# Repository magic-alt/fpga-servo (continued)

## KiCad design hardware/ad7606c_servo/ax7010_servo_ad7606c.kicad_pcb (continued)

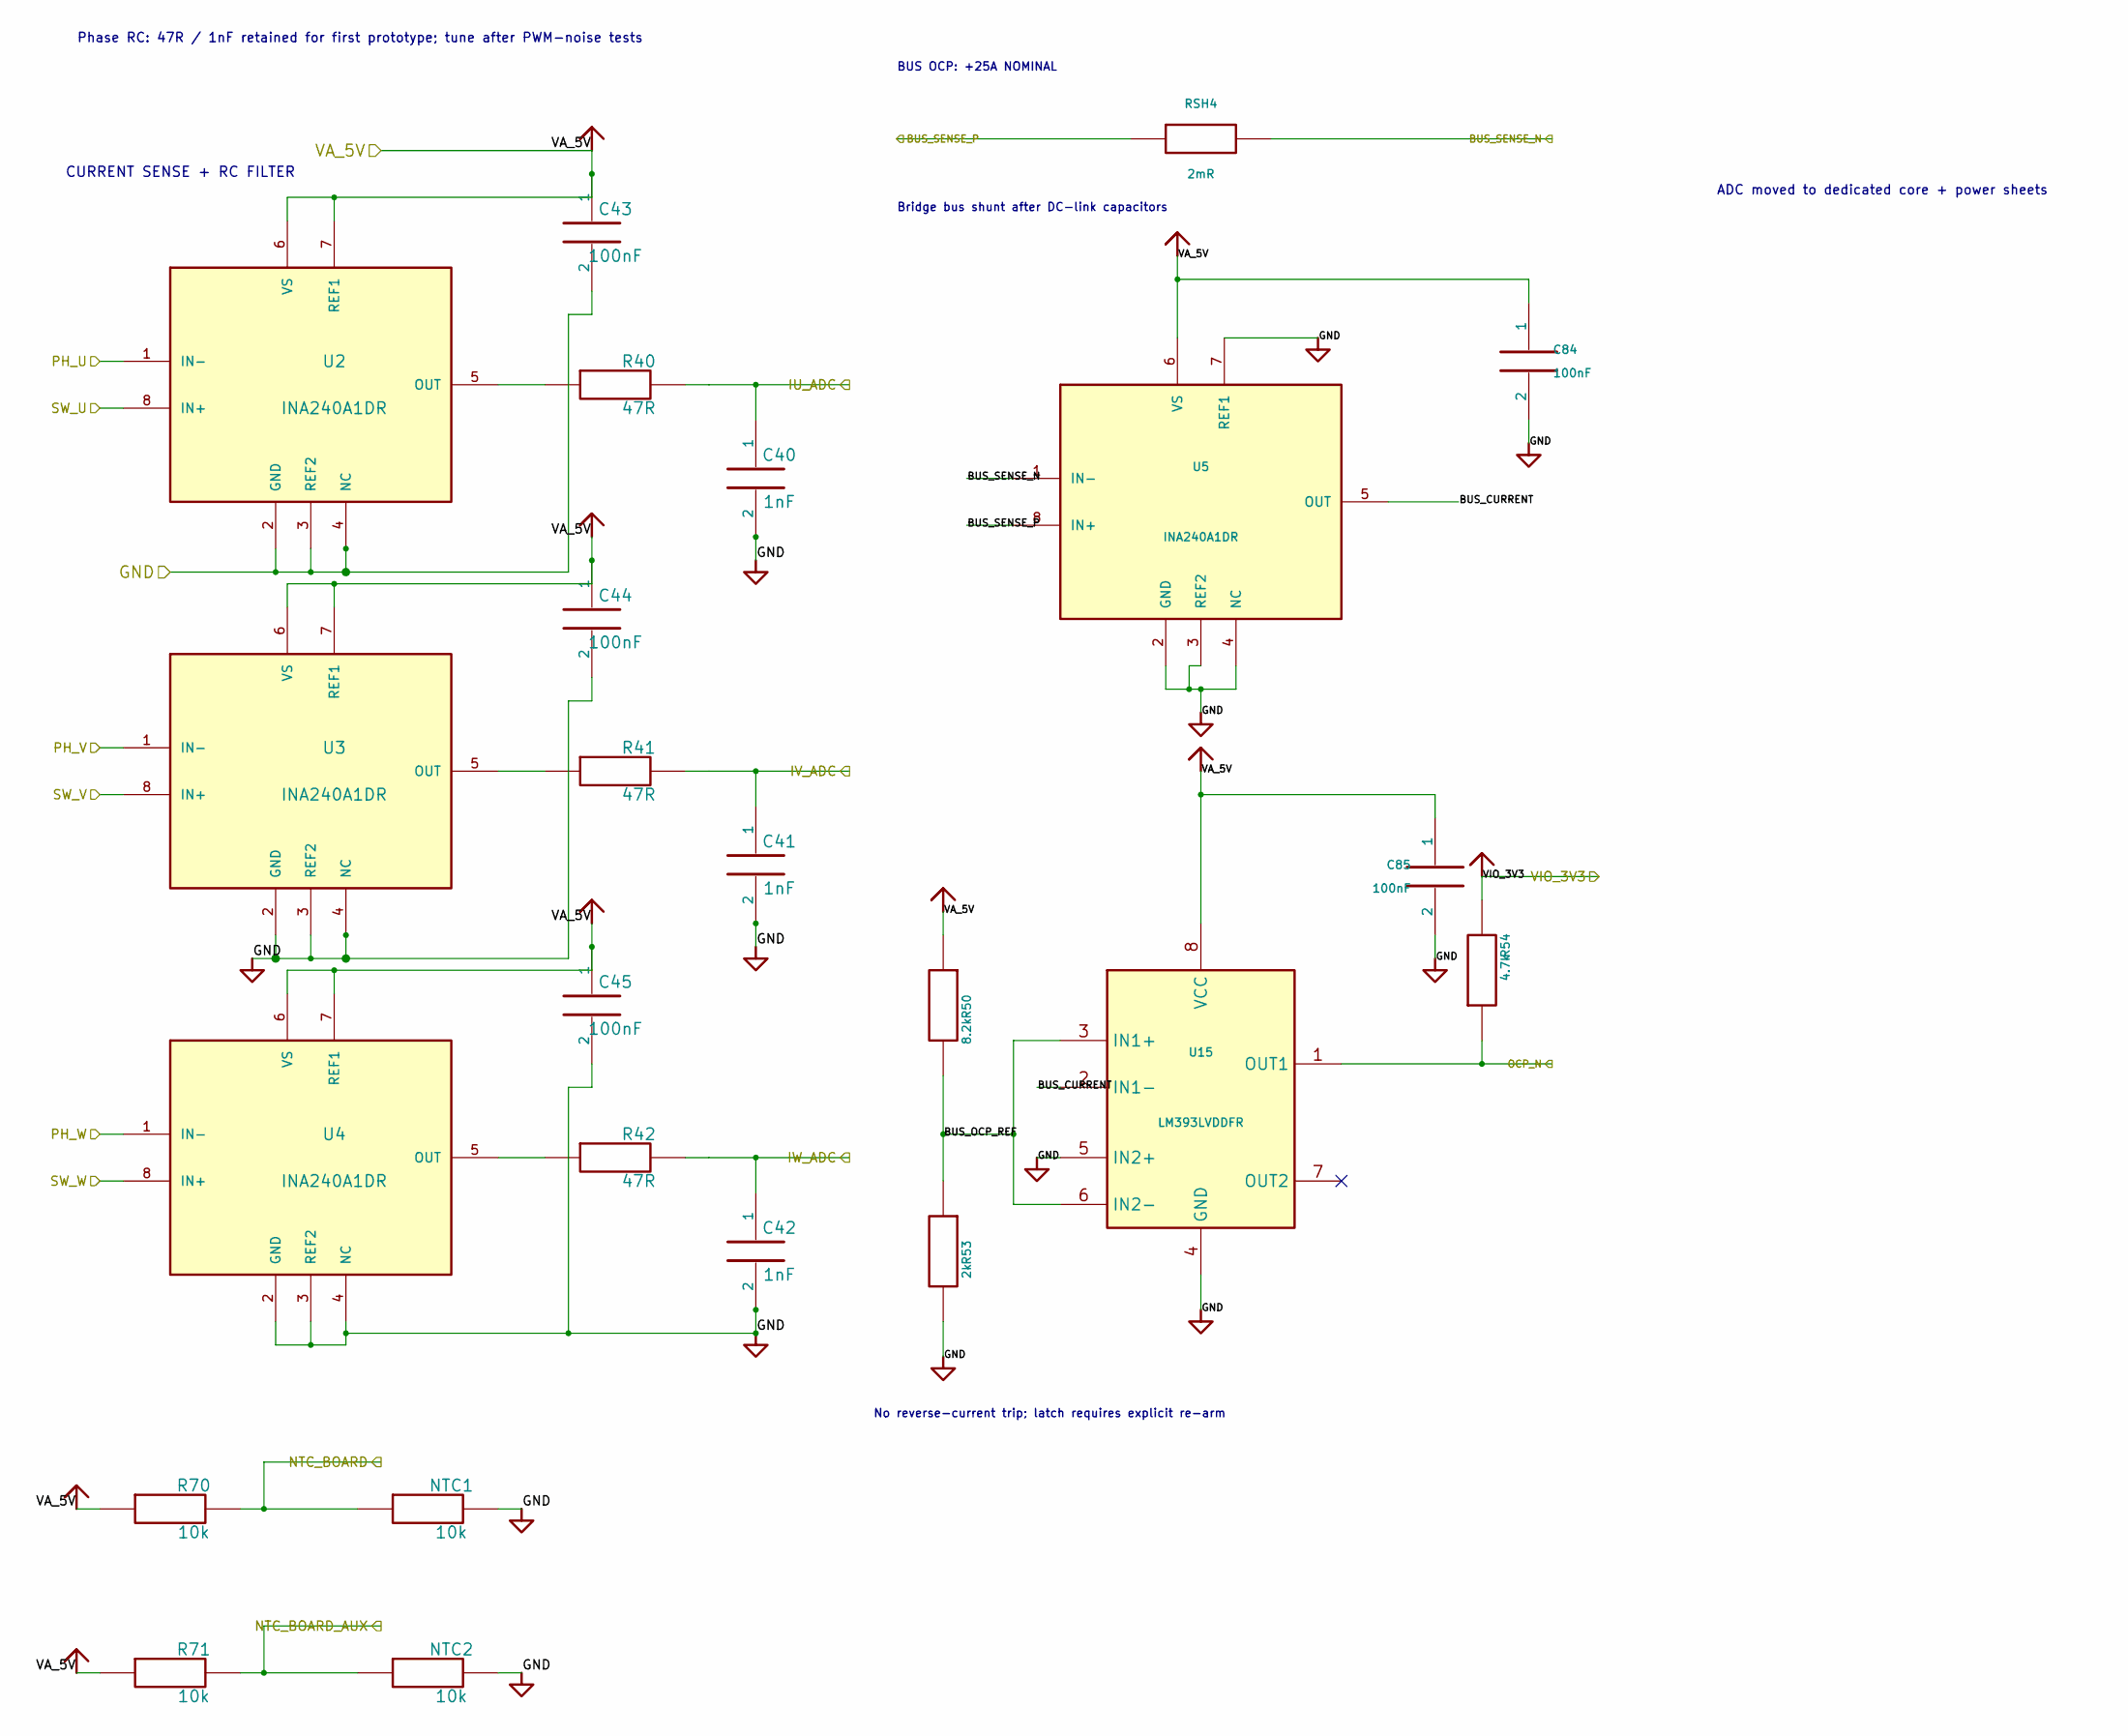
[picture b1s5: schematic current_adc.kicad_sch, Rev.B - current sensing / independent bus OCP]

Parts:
C40, C41, C42: 1nF; C_0603_1608Metric; MPN 0603CG102J101NT; LCSC C88489
C43, C44, C45, C84, C85: 100nF; C_0603_1608Metric; MPN 0603B104K500NT; LCSC C30926
NTC1, NTC2: 10k; NTC_0603_Shiheng_KUU; MPN CMFA 103F3950; LCSC C2889049
R40, R41, R42: 47R; R_0603_1608Metric; MPN RS-03K47R0FT; LCSC C140087
R50: 8.2k; R_0603_1608Metric; Tolerance 0.1%; MPN PTFR0603B8K20P9; LCSC C351624
R53: 2k; R_0603_1608Metric; Tolerance 0.1%; MPN TD03G2001BT; LCSC C666953
R54: 4.7k; R_0603_1608Metric; MPN RS-03K4701FT; LCSC C116693
R70, R71: 10k; R_0603_1608Metric; MPN TD03G1002BT; LCSC C667034
RSH4: 2mR; HoYLR2512_Kelvin; MPN HoYLR2512-3W-2mR-1%; LCSC C5375458
U2, U3, U4, U5: INA240A1DR; TI_D0008A_SOIC8_P1.27mm; MPN INA240A1DR; LCSC C2060769
U15: LM393LVDDFR; TI_DDF0008A; MPN LM393LVDDFR; LCSC C5213974

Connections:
/GND: C40.2, C41.2, C42.2, C43.2, C44.2, C45.2, C84.2, C85.2, NTC1.2, NTC2.2, R53.2, U2.2 (GND), U2.3 (REF2), U2.4 (NC), U3.2 (GND), U3.3 (REF2), U3.4 (NC), U4.2 (GND), U4.3 (REF2), U4.4 (NC), U5.2 (GND), U5.3 (REF2), U5.4 (NC), U5.7 (REF1), U15.4 (GND), U15.5 (IN2+); also elsewhere on the board
/IU_ADC: C40.1, R40.2; also elsewhere on the board
/IV_ADC: C41.1, R41.2; also elsewhere on the board
/IW_ADC: C42.1, R42.2; also elsewhere on the board
/NTC_BOARD: NTC1.1, R70.2; also elsewhere on the board
/NTC_BOARD_AUX: NTC2.1, R71.2; also elsewhere on the board
/OCP_N: R54.1, U15.1 (OUT1); also elsewhere on the board
/PH_U: U2.1 (IN-); also elsewhere on the board
/PH_V: U3.1 (IN-); also elsewhere on the board
/PH_W: U4.1 (IN-); also elsewhere on the board
/SW_U: U2.8 (IN+); also elsewhere on the board
/SW_V: U3.8 (IN+); also elsewhere on the board
/SW_W: U4.8 (IN+); also elsewhere on the board
/VA_5V: C43.1, C44.1, C45.1, C84.1, C85.1, R50.1, R70.1, R71.1, U2.6 (VS), U2.7 (REF1), U3.6 (VS), U3.7 (REF1), U4.6 (VS), U4.7 (REF1), U5.6 (VS), U15.8 (VCC); also elsewhere on the board
/VBUS_BRIDGE: RSH4.2, U5.1 (IN-); also elsewhere on the board
/VBUS_PROT: RSH4.1, U5.8 (IN+); also elsewhere on the board
/VIO_3V3: R54.2; also elsewhere on the board
/current_adc/BUS_CURRENT: U5.5 (OUT), U15.2 (IN1-)
/current_adc/BUS_OCP_REF: R50.2, R53.1, U15.3 (IN1+), U15.6 (IN2-)
unnamed: R40.1, U2.5 (OUT)
unnamed: R41.1, U3.5 (OUT)
unnamed: R42.1, U4.5 (OUT)

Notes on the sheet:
CURRENT SENSE + RC FILTER
BUS OCP: +25A NOMINAL
No reverse-current trip; latch requires explicit re-arm
Bridge bus shunt after DC-link capacitors
ADC moved to dedicated core + power sheets
Phase RC: 47R / 1nF retained for first prototype; tune after PWM-noise tests

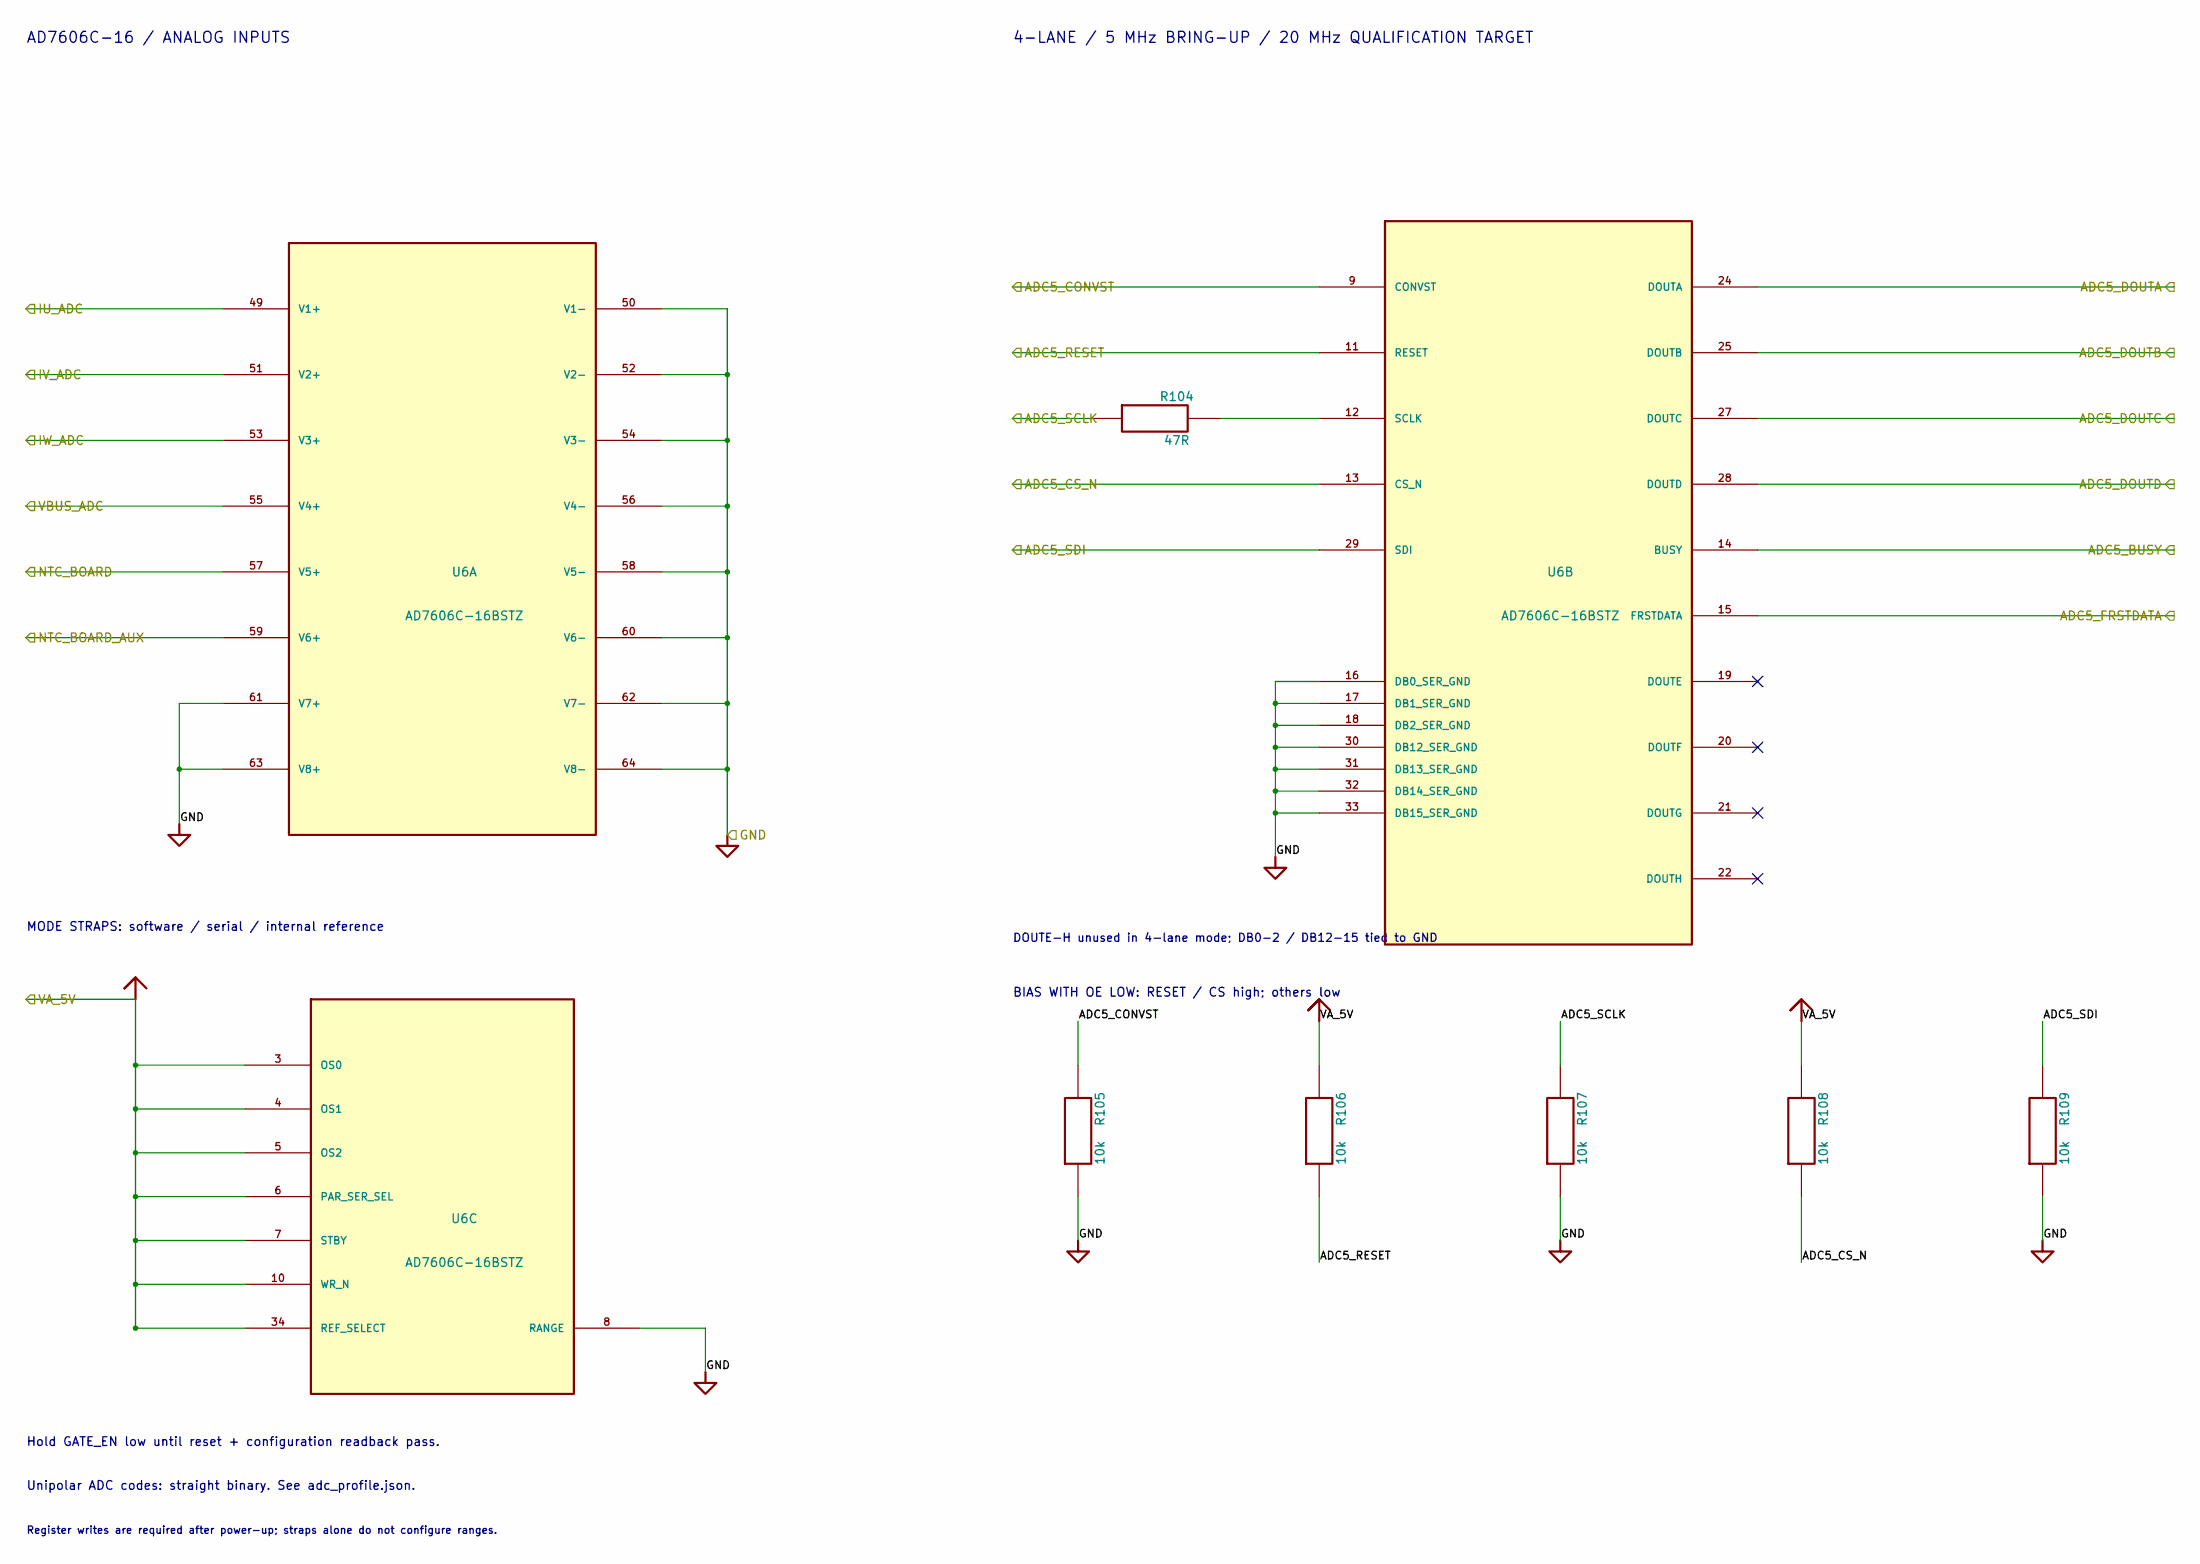
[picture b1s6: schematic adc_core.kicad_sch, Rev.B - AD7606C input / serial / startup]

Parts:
R104: 47R; R_0603_1608Metric; MPN RS-03K47R0FT; LCSC C140087
R105, R106, R107, R108, R109: 10k; R_0603_1608Metric; MPN ABD03K1002FT; LCSC C5139509
U6: AD7606C-16BSTZ; LQFP-64_10x10mm_P0.5mm; MPN AD7606C-16BSTZ; LCSC C5371769

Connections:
/ADC5_BUSY: U6.14 (BUSY); also elsewhere on the board
/ADC5_CONVST: R105.2, U6.9 (CONVST); also elsewhere on the board
/ADC5_CS_N: R108.1, U6.13 (CS_N); also elsewhere on the board
/ADC5_DOUTA: U6.24 (DOUTA); also elsewhere on the board
/ADC5_DOUTB: U6.25 (DOUTB); also elsewhere on the board
/ADC5_DOUTC: U6.27 (DOUTC); also elsewhere on the board
/ADC5_DOUTD: U6.28 (DOUTD); also elsewhere on the board
/ADC5_FRSTDATA: U6.15 (FRSTDATA); also elsewhere on the board
/ADC5_RESET: R106.1, U6.11 (RESET); also elsewhere on the board
/ADC5_SCLK: R104.1, R107.2; also elsewhere on the board
/ADC5_SDI: R109.2, U6.29 (SDI); also elsewhere on the board
/GND: R105.1, R107.1, R109.1, U6.8 (RANGE), U6.16 (DB0_SER_GND), U6.17 (DB1_SER_GND), U6.18 (DB2_SER_GND), U6.30 (DB12_SER_GND), U6.31 (DB13_SER_GND), U6.32 (DB14_SER_GND), U6.33 (DB15_SER_GND), U6.50 (V1-), U6.52 (V2-), U6.54 (V3-), U6.56 (V4-), U6.58 (V5-), U6.60 (V6-), U6.61 (V7+), U6.62 (V7-), U6.63 (V8+), U6.64 (V8-); also elsewhere on the board
/IU_ADC: U6.49 (V1+); also elsewhere on the board
/IV_ADC: U6.51 (V2+); also elsewhere on the board
/IW_ADC: U6.53 (V3+); also elsewhere on the board
/NTC_BOARD: U6.57 (V5+); also elsewhere on the board
/NTC_BOARD_AUX: U6.59 (V6+); also elsewhere on the board
/VA_5V: R106.2, R108.2, U6.3 (OS0), U6.4 (OS1), U6.5 (OS2), U6.6 (PAR_SER_SEL), U6.7 (STBY), U6.10 (WR_N), U6.34 (REF_SELECT); also elsewhere on the board
/VBUS_ADC: U6.55 (V4+); also elsewhere on the board
unnamed: R104.2, U6.12 (SCLK)

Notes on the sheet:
AD7606C-16 / ANALOG INPUTS
4-LANE / 5 MHz BRING-UP / 20 MHz QUALIFICATION TARGET
DOUTE-H unused in 4-lane mode; DB0-2 / DB12-15 tied to GND
MODE STRAPS: software / serial / internal reference
BIAS WITH OE LOW: RESET / CS high; others low
Hold GATE_EN low until reset + configuration readback pass.
Unipolar ADC codes: straight binary. See adc_profile.json.
Register writes are required after power-up; straps alone do not configure ranges.

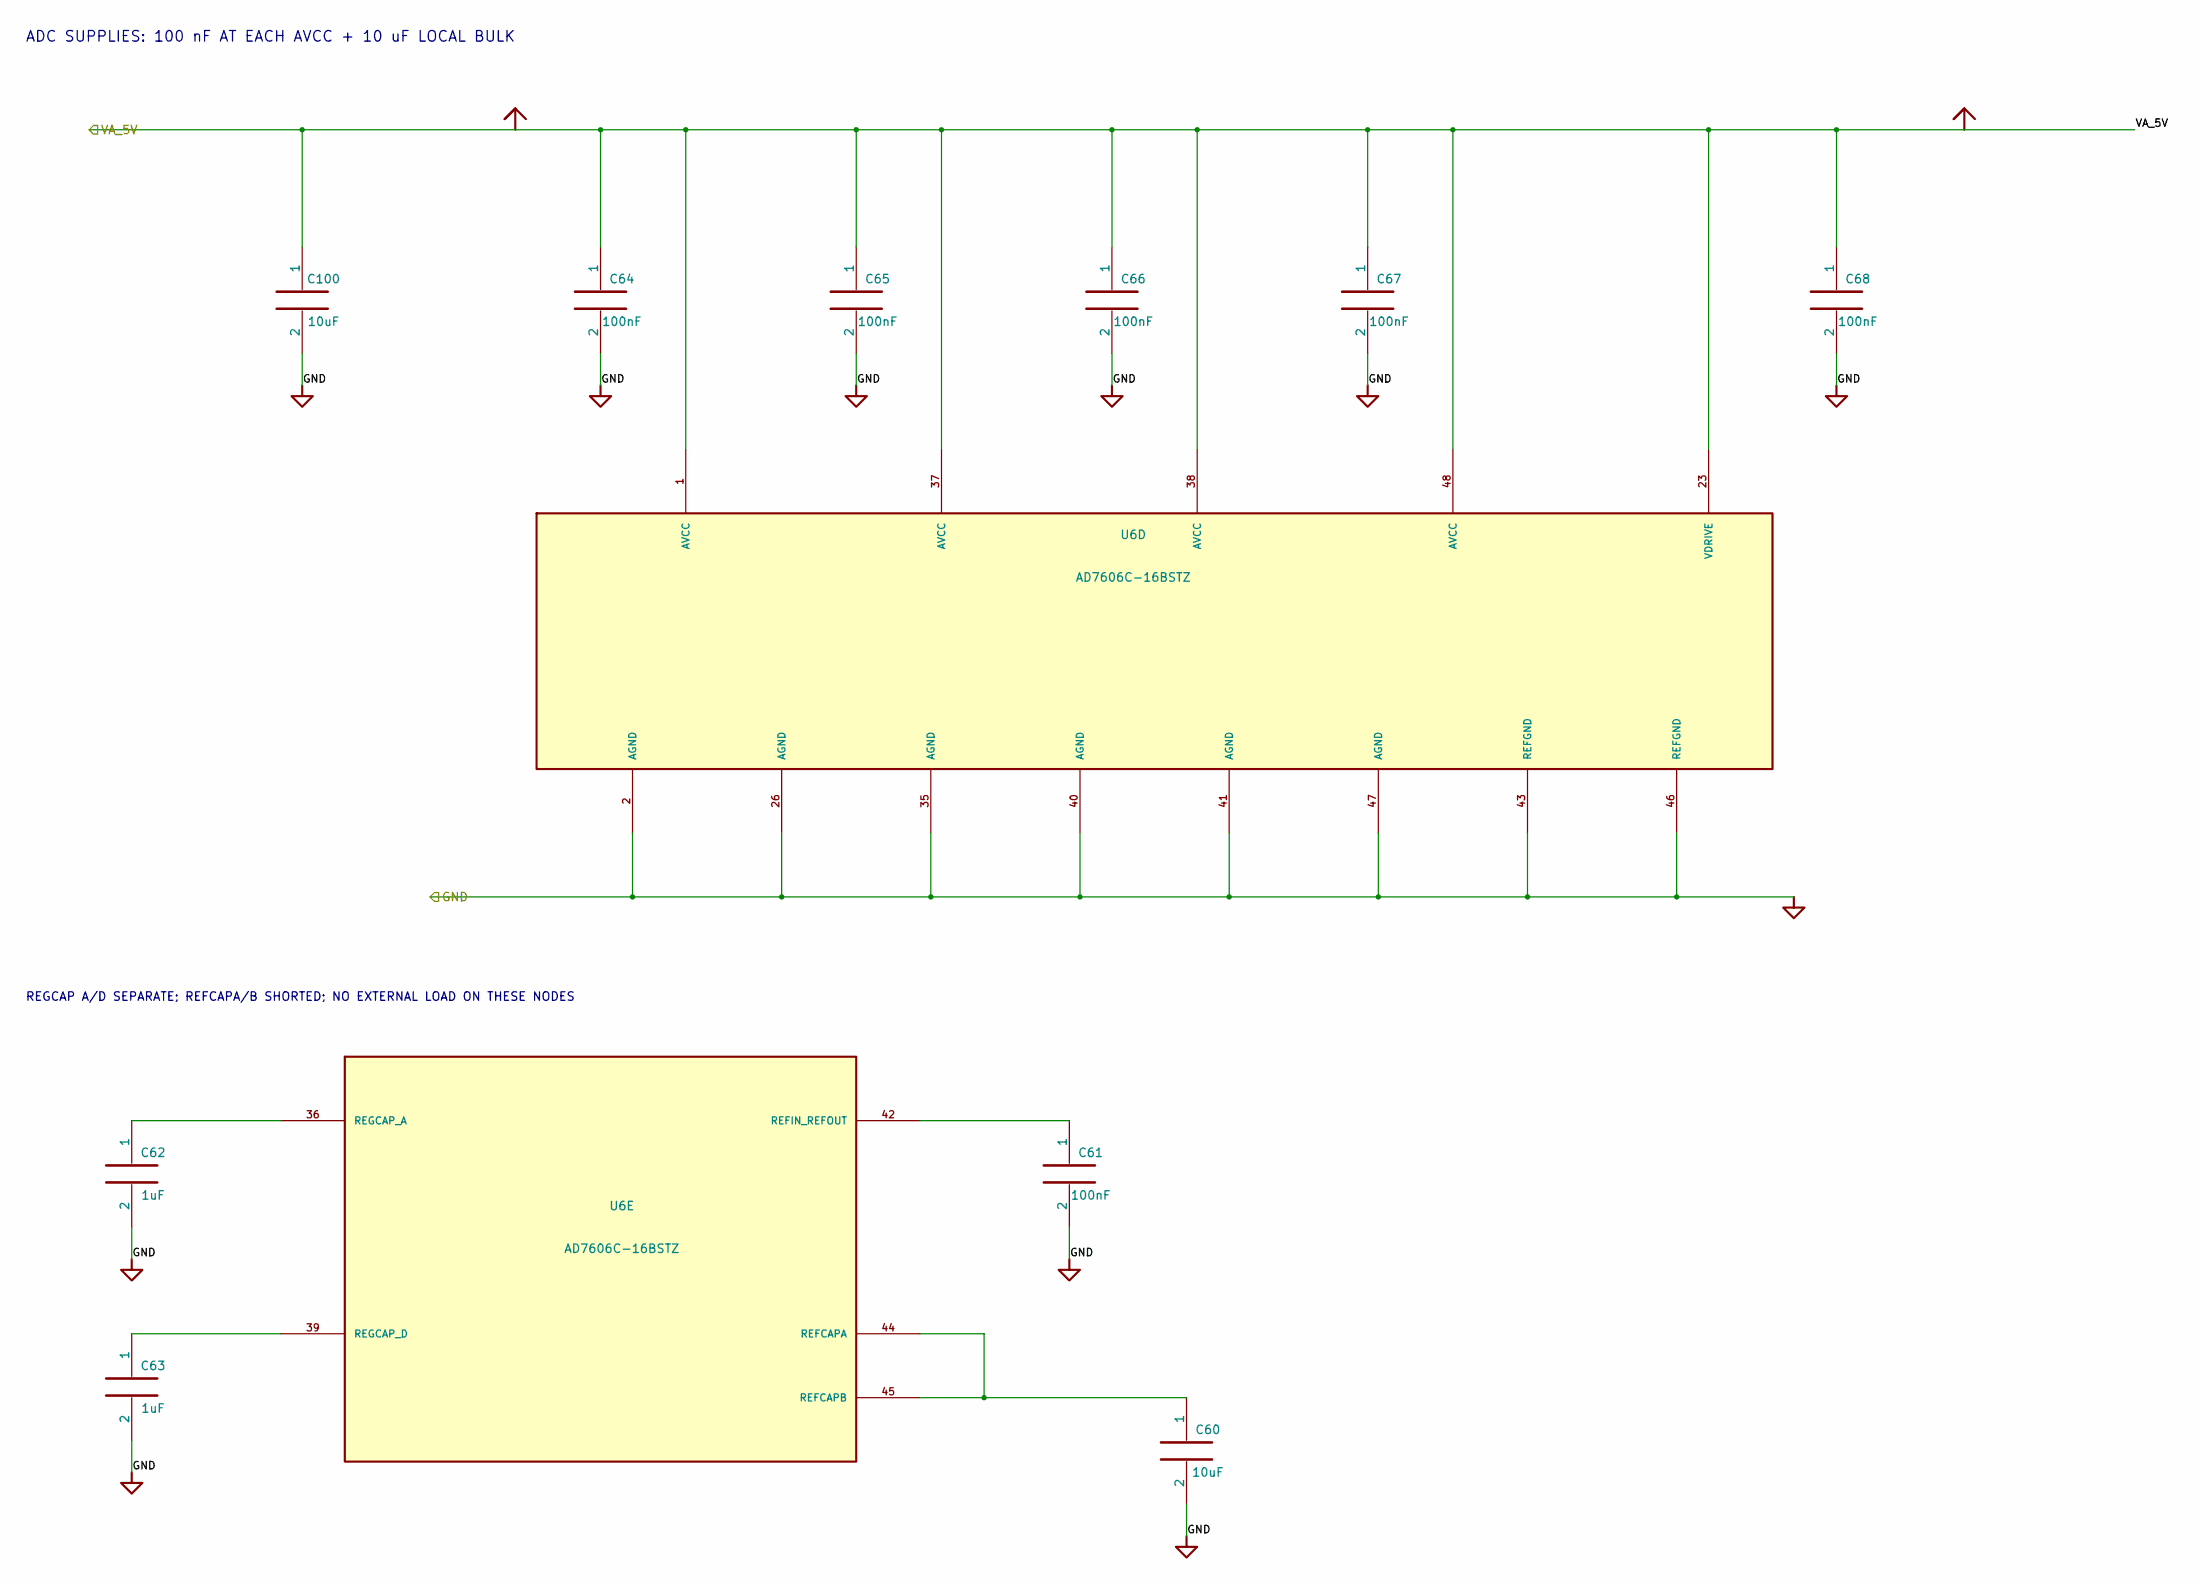
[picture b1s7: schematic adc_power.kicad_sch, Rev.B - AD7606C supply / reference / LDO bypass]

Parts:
C60, C100: 10uF; C_0805_2012Metric; MPN HGC0805R7106K250NSLJ; LCSC C33546010
C61, C64, C65, C66, C67, C68: 100nF; C_0603_1608Metric; MPN 0603B104K500NT; LCSC C30926
C62, C63: 1uF; C_0603_1608Metric; MPN 0603B105K250NT; LCSC C59302
U6: AD7606C-16BSTZ; LQFP-64_10x10mm_P0.5mm; MPN AD7606C-16BSTZ; LCSC C5371769

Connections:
/GND: C60.2, C61.2, C62.2, C63.2, C64.2, C65.2, C66.2, C67.2, C68.2, C100.2, U6.2 (AGND), U6.26 (AGND), U6.35 (AGND), U6.40 (AGND), U6.41 (AGND), U6.43 (REFGND), U6.46 (REFGND), U6.47 (AGND); also elsewhere on the board
/VA_5V: C64.1, C65.1, C66.1, C67.1, C68.1, C100.1, U6.1 (AVCC), U6.23 (VDRIVE), U6.37 (AVCC), U6.38 (AVCC), U6.48 (AVCC); also elsewhere on the board
unnamed: C60.1, U6.44 (REFCAPA), U6.45 (REFCAPB)
unnamed: C61.1, U6.42 (REFIN_REFOUT)
unnamed: C62.1, U6.36 (REGCAP_A)
unnamed: C63.1, U6.39 (REGCAP_D)

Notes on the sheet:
ADC SUPPLIES: 100 nF AT EACH AVCC + 10 uF LOCAL BULK
REGCAP A/D SEPARATE; REFCAPA/B SHORTED; NO EXTERNAL LOAD ON THESE NODES

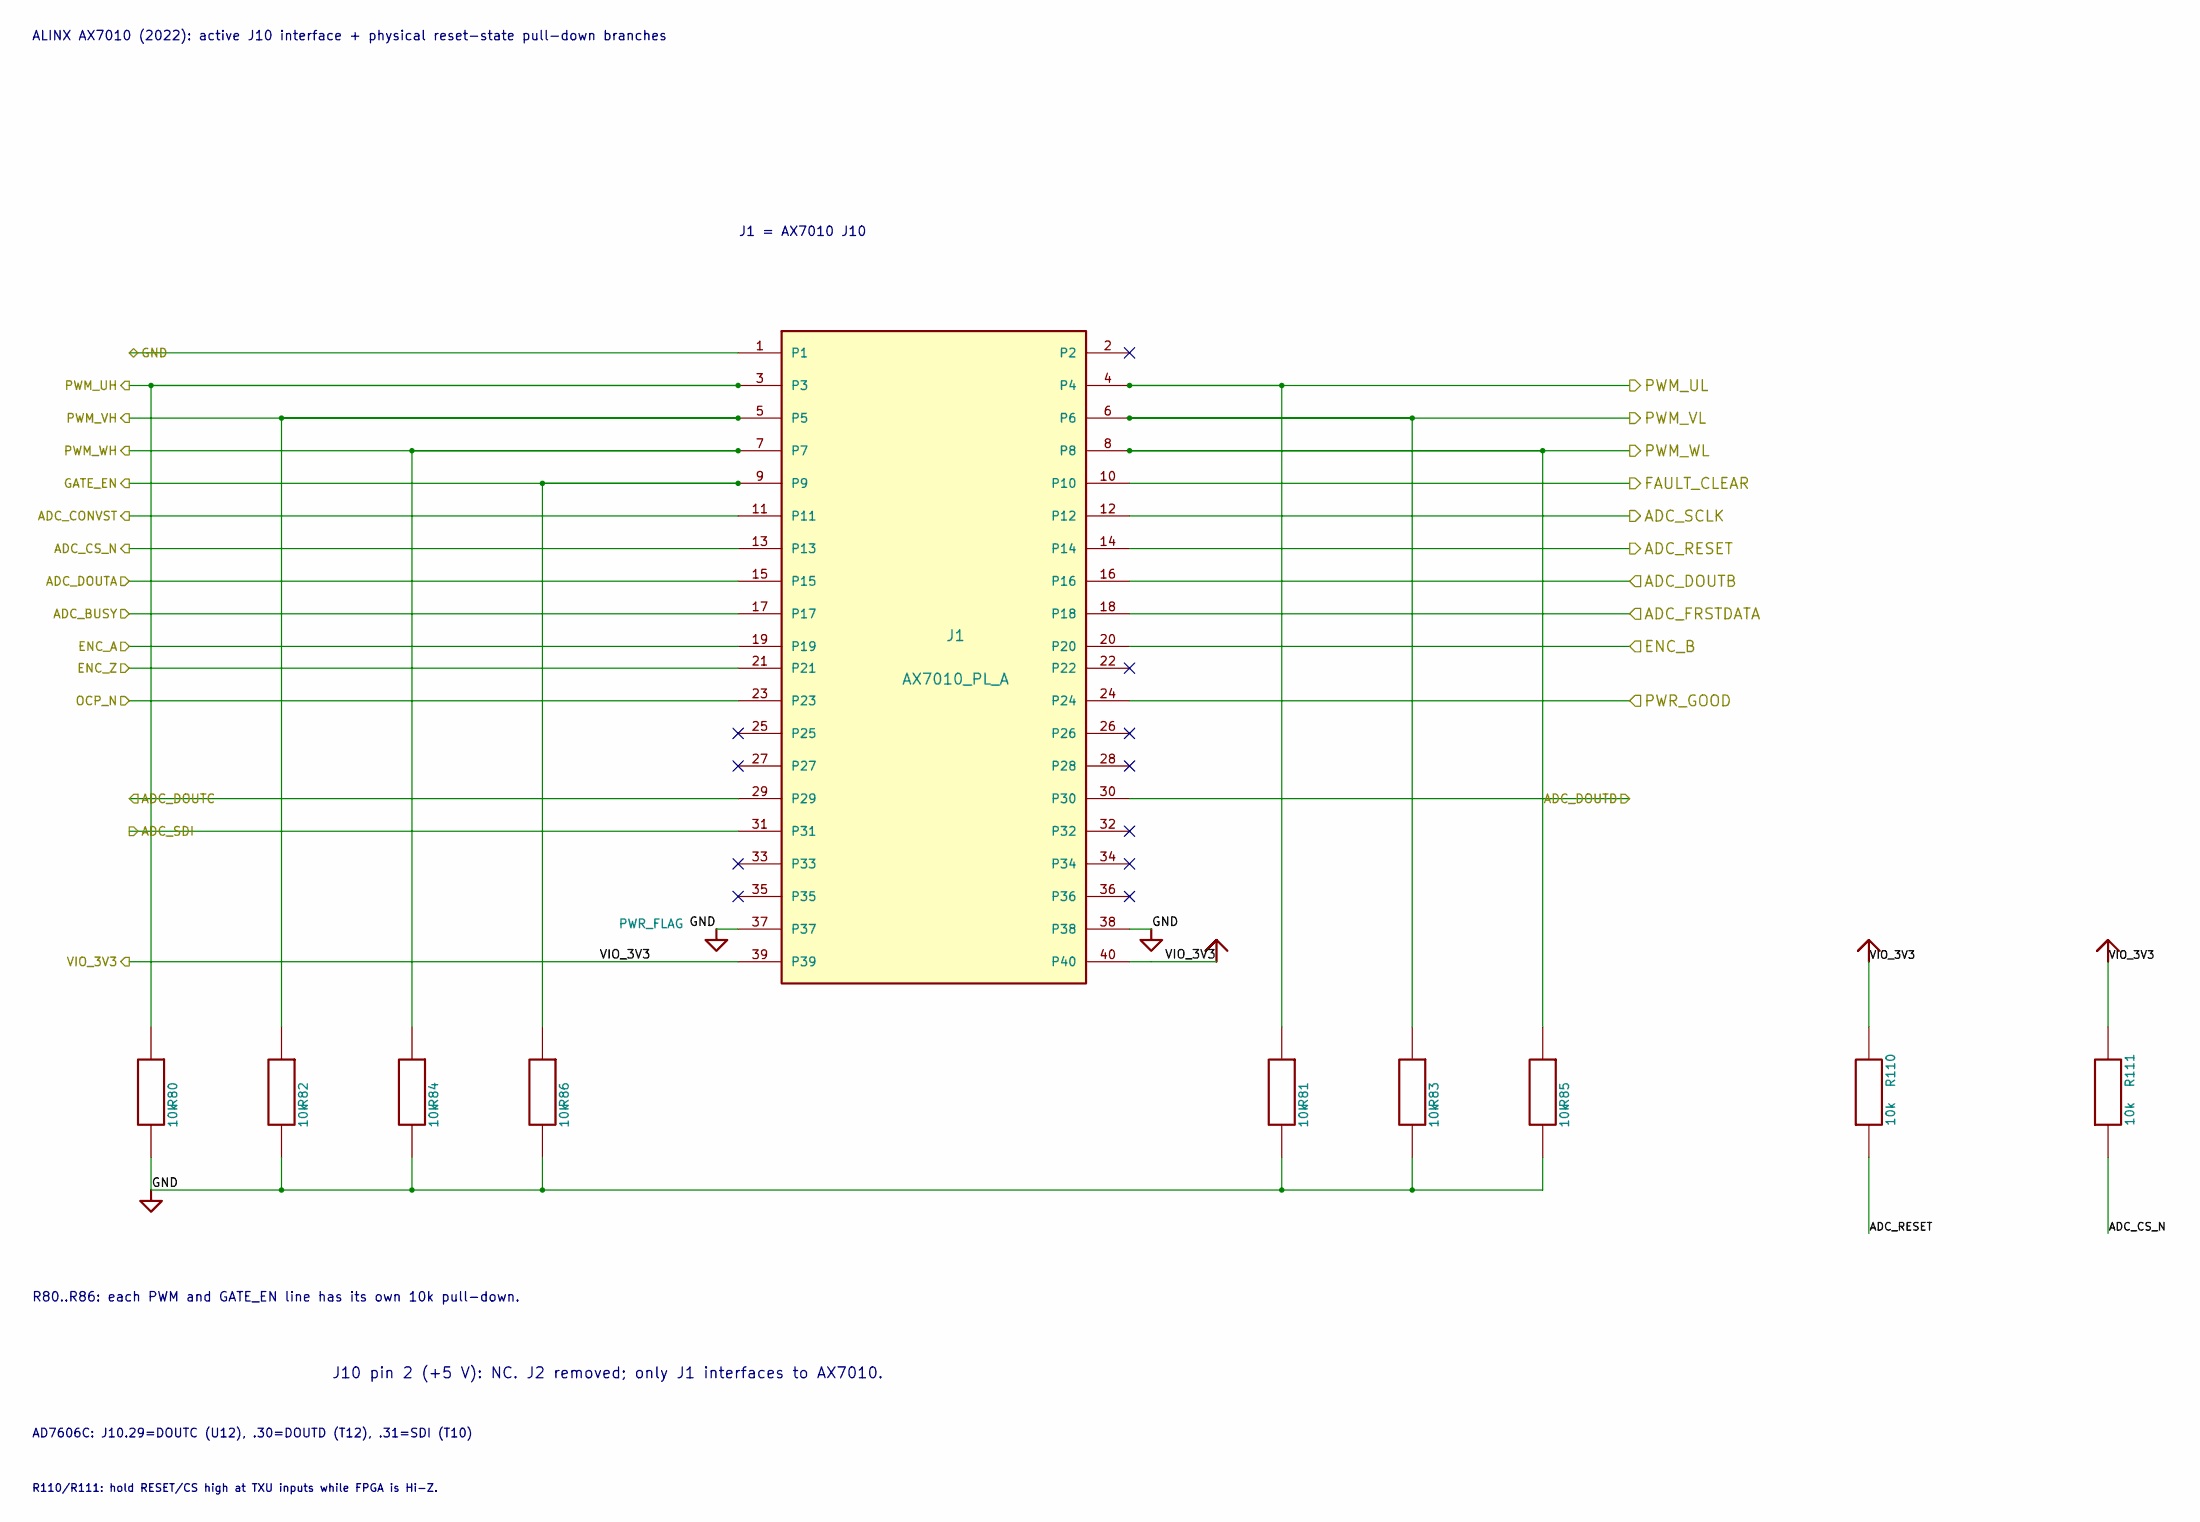
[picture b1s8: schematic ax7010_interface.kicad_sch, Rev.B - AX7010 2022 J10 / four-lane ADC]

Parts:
J1: AX7010_PL_A; JILN_3210_2x20_P2.54mm_D1.02; MPN 321040SG0ABK00A01; LCSC C601944
R80, R81, R82, R83, R84, R85, R86, R110, R111: 10k; R_0603_1608Metric; MPN ABD03K1002FT; LCSC C5139509

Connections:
/ADC_BUSY: J1.17; also elsewhere on the board
/ADC_CONVST: J1.11; also elsewhere on the board
/ADC_CS_N: J1.13, R111.1; also elsewhere on the board
/ADC_DOUTA: J1.15; also elsewhere on the board
/ADC_DOUTB: J1.16; also elsewhere on the board
/ADC_DOUTC: J1.29; also elsewhere on the board
/ADC_DOUTD: J1.30; also elsewhere on the board
/ADC_FRSTDATA: J1.18; also elsewhere on the board
/ADC_RESET: J1.14, R110.1; also elsewhere on the board
/ADC_SCLK: J1.12; also elsewhere on the board
/ADC_SDI: J1.31; also elsewhere on the board
/ENC_A: J1.19; also elsewhere on the board
/ENC_B: J1.20; also elsewhere on the board
/ENC_Z: J1.21; also elsewhere on the board
/FAULT_CLEAR: J1.10; also elsewhere on the board
/GATE_EN: J1.9, R86.1; also elsewhere on the board
/GND: J1.1, J1.37, J1.38, R80.2, R81.2, R82.2, R83.2, R84.2, R85.2, R86.2; also elsewhere on the board
/OCP_N: J1.23; also elsewhere on the board
/PWM_UH: J1.3, R80.1; also elsewhere on the board
/PWM_UL: J1.4, R81.1; also elsewhere on the board
/PWM_VH: J1.5, R82.1; also elsewhere on the board
/PWM_VL: J1.6, R83.1; also elsewhere on the board
/PWM_WH: J1.7, R84.1; also elsewhere on the board
/PWM_WL: J1.8, R85.1; also elsewhere on the board
/PWR_GOOD: J1.24; also elsewhere on the board
/VIO_3V3: J1.39, J1.40, R110.2, R111.2; also elsewhere on the board

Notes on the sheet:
ALINX AX7010 (2022): active J10 interface + physical reset-state pull-down branches
J1 = AX7010 J10
R80..R86: each PWM and GATE_EN line has its own 10k pull-down.
J10 pin 2 (+5 V): NC. J2 removed; only J1 interfaces to AX7010.
R110/R111: hold RESET/CS high at TXU inputs while FPGA is Hi-Z.
AD7606C: J10.29=DOUTC (U12), .30=DOUTD (T12), .31=SDI (T10)

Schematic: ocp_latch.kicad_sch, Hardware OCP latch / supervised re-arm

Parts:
C86, C87, C88, C89, C90, C91, C93: 100nF; C_0603_1608Metric; MPN 0603B104K500NT; LCSC C30926
C92: 1nF; C_0603_1608Metric; MPN 0603CG102J101NT; LCSC C88489
C94: 100nF; C_1206_3216Metric; MPN GRT31C5C1H104FA02L; LCSC C3839854
R87, R90, R91: 10k; R_0603_1608Metric; MPN ABD03K1002FT; LCSC C5139509
R88: 1k; R_0603_1608Metric; MPN ABD03K1001FT; LCSC C5125843
R89: 100k; R_0603_1608Metric; MPN RS-03K1003FT; LCSC C115320
R92: 3.24k; R_0603_1608Metric; Tolerance 0.1%; MPN TD03G3241BT; LCSC C666977
R93: 1k; R_0603_1608Metric; Tolerance 0.05%; MPN PTFR0603Q1K00N9; LCSC C23067434
TP5: ARMED; TestPoint_Pad_D1.5mm
U20: SN74LVC1G74; TI_DCU0008A_VSSOP8_P0.5mm; MPN SN74LVC1G74DCUR; LCSC C70285
U21: SN74LVC1G17; SOT-23-5; MPN SN74LVC1G17DBVR; LCSC C7836
U22: SN74LVC1G14; SOT-23-5; MPN SN74LVC1G14DBVR; LCSC C7835
U23: SN74LVC1G11; SOT-363_SC-70-6; MPN SN74LVC1G11DCKR; LCSC C529281
U24: TPS3808G33; SOT-23-6; MPN TPS3808G33DBVR; LCSC C43698
U25: TPS389001DSER; Texas_DSE0006A_WSON-6_1.5x1.5mm; MPN TPS389001DSER; LCSC C1509297
U26: SN74LVC3G17; TI_DCU0008A_VSSOP8_P0.5mm; MPN SN74LVC3G17DCUR; LCSC C68245

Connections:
/ARMED: R90.1, TP5.1 (1_1), U20.5 (Q); also elsewhere on the board
/FAULT_CLEAR: R87.1, R88.1; also elsewhere on the board
/GATE_EN: U22.2 (A); also elsewhere on the board
/GND: C86.2, C87.2, C88.2, C89.2, C90.2, C91.2, C92.2, C93.2, C94.2, R87.2, R90.2, R91.2, R93.2, U20.4 (GND), U21.3 (GND), U22.3 (GND), U23.2 (GND), U24.2 (GND), U25.2 (GND), U26.4 (GND); also elsewhere on the board
/OCP_N: U26.3 (2A); also elsewhere on the board
/PWR_GOOD: U26.6 (3A); also elsewhere on the board
/PWR_READY: U23.3 (B), U26.2 (3Y); also elsewhere on the board
/VA_5V: R92.1; also elsewhere on the board
/VIO_3V3: C86.1, C87.1, C88.1, C89.1, C90.1, C91.1, C93.1, R89.1, U20.7 (~PRE), U20.8 (VCC), U21.5 (VCC), U22.5 (VCC), U23.5 (VCC), U24.3 (~MR), U24.5 (SENSE), U24.6 (VDD), U25.3 (~MR), U25.4 (VDD), U26.8 (VCC); also elsewhere on the board
/ocp_latch/CLEAR_CLK: U20.1 (CLK), U21.4 (Y)
/ocp_latch/CLEAR_FILT: C92.1, R88.2, U21.2 (A)
/ocp_latch/DISABLED: U20.2 (D), U22.4 (~Y)
/ocp_latch/HEALTHY_N: R91.1, U20.6 (~CLR), U23.4 (Y)
/ocp_latch/OCP_OK: U23.1 (A), U26.5 (2Y)
/ocp_latch/POR_N: R89.2, U24.1 (~RESET), U25.6 (~RESET), U26.1 (1A)
/ocp_latch/POR_OK: U23.6 (C), U26.7 (1Y)
unnamed: C94.1, U25.5 (CT)
unnamed: R92.2, R93.1, U25.1 (SENSE)

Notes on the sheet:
HARDWARE ARM: any OCP / power fault clears Q. Recovery alone never re-arms.
CLEAR: EN=0, healthy >=1ms, CLEAR high >=10us; wait >=10us before EN=1.
U24 CT open: 12..28ms. U25 CT=100nF: ~107ms; VA5 trip nominal 4.876V. Dynamic qualification OPEN.
CLEAR held high through a fault cannot re-arm. Raw fault pulse timing needs validation.
U20..U26: local 100nF bypass; reset release passes through U26 Schmitt buffers.

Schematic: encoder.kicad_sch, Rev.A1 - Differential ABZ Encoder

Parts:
C70: 100nF; C_0603_1608Metric; MPN 0603B104K500NT; LCSC C30926
C71: 4.7uF; C_0805_2012Metric; MPN CGA0805X7R475K250MT; LCSC C6119942
F2: 0.5A_PTC_ENCODER_5V; Fuse_1812_4532Metric; MPN ASMD1812-050; LCSC C135358
J5: ABZ_DIFF_ENCODER; JILN_3210_2x05_P2.54mm_D1.02; MPN 321010SG0ABK00A01; LCSC C429962
RT1, RT2, RT3: 120R; R_0603_1608Metric; not fitted
U7: AM26LV32EIPWR; TSSOP-16_4.4x5mm_P0.65mm; MPN AM26LV32EIPWR; LCSC C404024
U19: TPD6E05U06RVZR; TI_RVZ0014A_W025; MPN TPD6E05U06RVZR; LCSC C962978

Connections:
/ENC_A: U7.3 (1Y); also elsewhere on the board
/ENC_B: U7.5 (2Y); also elsewhere on the board
/ENC_Z: U7.11 (3Y); also elsewhere on the board
/GND: C70.2, C71.2, J5.8 (GND), U7.8 (GND), U7.12 (G_N), U19.5 (GND), U19.10 (GND); also elsewhere on the board
/VA_5V: F2.1; also elsewhere on the board
/VIO_3V3: C70.1, C71.1, U7.4 (G), U7.16 (VCC); also elsewhere on the board
/encoder/ENC_5V: F2.2, J5.7 (5V)
/encoder/ENC_A_N: J5.2 (A-), RT1.2, U7.1 (1A-), U19.13 (IO2)
/encoder/ENC_A_P: J5.1 (A+), RT1.1, U7.2 (1A+), U19.14 (IO1)
/encoder/ENC_B_N: J5.4 (B-), RT2.2, U7.7 (2A-), U19.11 (IO4)
/encoder/ENC_B_P: J5.3 (B+), RT2.1, U7.6 (2A+), U19.12 (IO3)
/encoder/ENC_Z_N: J5.6 (Z-), RT3.2, U7.9 (3A-), U19.8 (IO6)
/encoder/ENC_Z_P: J5.5 (Z+), RT3.1, U7.10 (3A+), U19.9 (IO5)

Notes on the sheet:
Local wiring: ABZ pairs, termination, ESD, receiver and encoder power.
A/B/Z are differential RS-422 pairs. 120R termination is fitted only when this board is the cable end.
U19: RVZ-14 / Texas_R-PUSON-N14. IO=14,13,12,11,9,8; GND=5,10; NC=1,2,3,4,6,7. Place beside J5.
AM26LV32E is powered from FPGA VIO_3V3 so its outputs cannot over-drive an unpowered AX7010 domain.
J5 -> differential pairs + selectable termination -> U7 receiver
U19 is a shunt ESD array: six IO taps; NC pads remain unconnected.

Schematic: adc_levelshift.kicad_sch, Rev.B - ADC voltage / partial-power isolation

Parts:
C101, C102, C103, C104, C105, C106: 100nF; C_0603_1608Metric; MPN 0603B104K500NT; LCSC C30926
R100, R101, R102, R103: 47R; R_0603_1608Metric; MPN RS-03K47R0FT; LCSC C140087
U27, U28, U29: TXU0204PWR; TSSOP-14_4.4x5mm_P0.65mm; MPN TXU0204PWR; LCSC UNVERIFIED

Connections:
/ADC5_BUSY: U29.11 (B3); also elsewhere on the board
/ADC5_CONVST: U27.13 (B1Y); also elsewhere on the board
/ADC5_CS_N: U28.12 (B2Y); also elsewhere on the board
/ADC5_DOUTA: U27.11 (B3); also elsewhere on the board
/ADC5_DOUTB: U27.10 (B4); also elsewhere on the board
/ADC5_DOUTC: U28.11 (B3); also elsewhere on the board
/ADC5_DOUTD: U28.10 (B4); also elsewhere on the board
/ADC5_FRSTDATA: U29.10 (B4); also elsewhere on the board
/ADC5_RESET: U27.12 (B2Y); also elsewhere on the board
/ADC5_SCLK: U28.13 (B1Y); also elsewhere on the board
/ADC5_SDI: U29.13 (B1Y); also elsewhere on the board
/ADC_BUSY: U29.4 (A3Y); also elsewhere on the board
/ADC_CONVST: U27.2 (A1); also elsewhere on the board
/ADC_CS_N: U28.3 (A2); also elsewhere on the board
/ADC_DOUTA: R100.1; also elsewhere on the board
/ADC_DOUTB: R101.1; also elsewhere on the board
/ADC_DOUTC: R102.1; also elsewhere on the board
/ADC_DOUTD: R103.1; also elsewhere on the board
/ADC_FRSTDATA: U29.5 (A4Y); also elsewhere on the board
/ADC_RESET: U27.3 (A2); also elsewhere on the board
/ADC_SCLK: U28.2 (A1); also elsewhere on the board
/ADC_SDI: U29.2 (A1); also elsewhere on the board
/GND: C101.2, C102.2, C103.2, C104.2, C105.2, C106.2, U27.7 (GND), U28.7 (GND), U29.3 (A2), U29.7 (GND); also elsewhere on the board
/PWR_READY: U27.8 (OE), U28.8 (OE), U29.8 (OE); also elsewhere on the board
/VA_5V: C102.1, C104.1, C106.1, U27.14 (VCCB), U28.14 (VCCB), U29.14 (VCCB); also elsewhere on the board
/VIO_3V3: C101.1, C103.1, C105.1, U27.1 (VCCA), U28.1 (VCCA), U29.1 (VCCA); also elsewhere on the board
unnamed: R100.2, U27.4 (A3Y)
unnamed: R101.2, U27.5 (A4Y)
unnamed: R102.2, U28.4 (A3Y)
unnamed: R103.2, U28.5 (A4Y)

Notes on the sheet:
ADC POWER-DOMAIN ISOLATION: FPGA 3.3 V <-> ADC VA_5V
U6 AVCC = VDRIVE = VA_5V; never connect AX7010 3.3 V directly to U6.23
OE follows PWR_READY: translators disable on supervised rail faults.
TI Ioff / VCC disconnect prevents back-power when either supply is off.
RESET / CS pulls are on the ADC side. Firmware must apply full RESET after OE is enabled.
Translate delay, J10 flight time and ADC delay must all be included in Vivado I/O timing.
